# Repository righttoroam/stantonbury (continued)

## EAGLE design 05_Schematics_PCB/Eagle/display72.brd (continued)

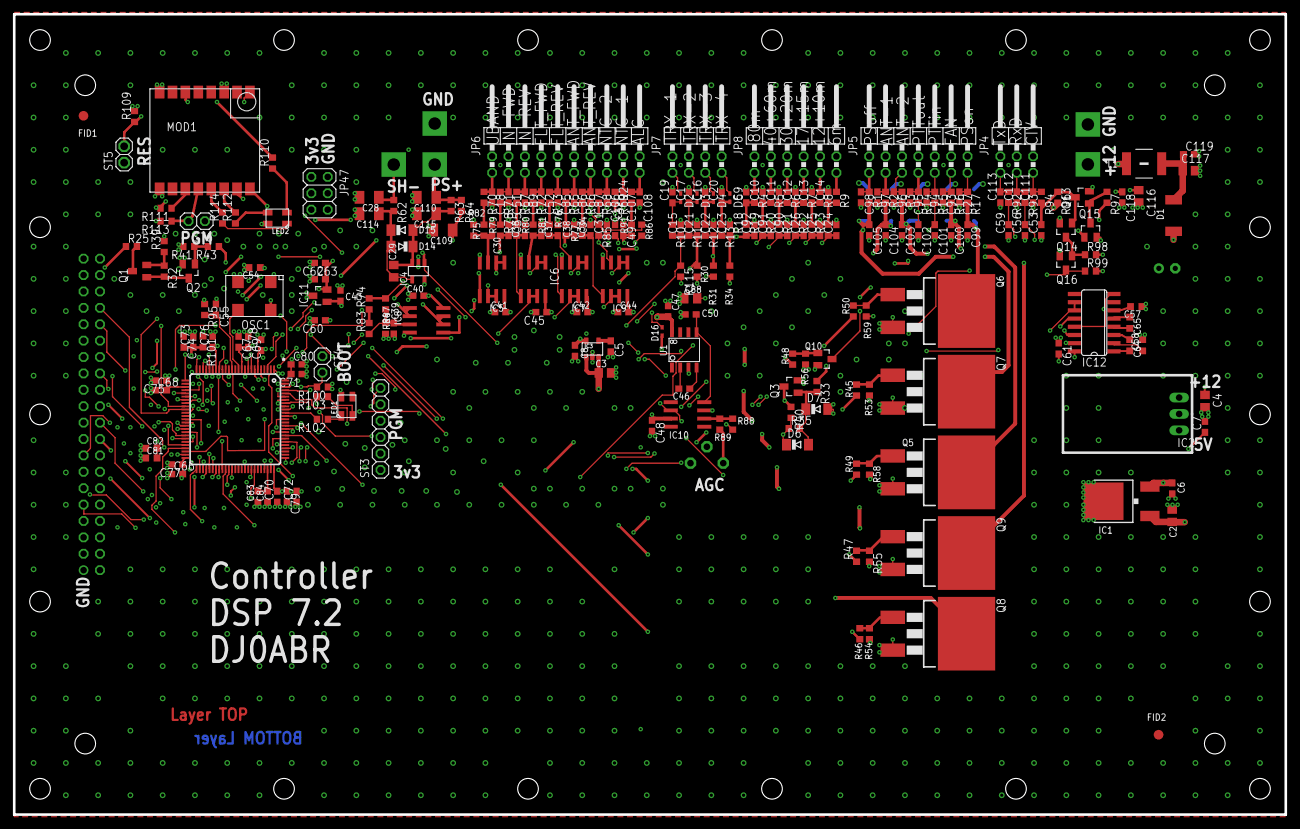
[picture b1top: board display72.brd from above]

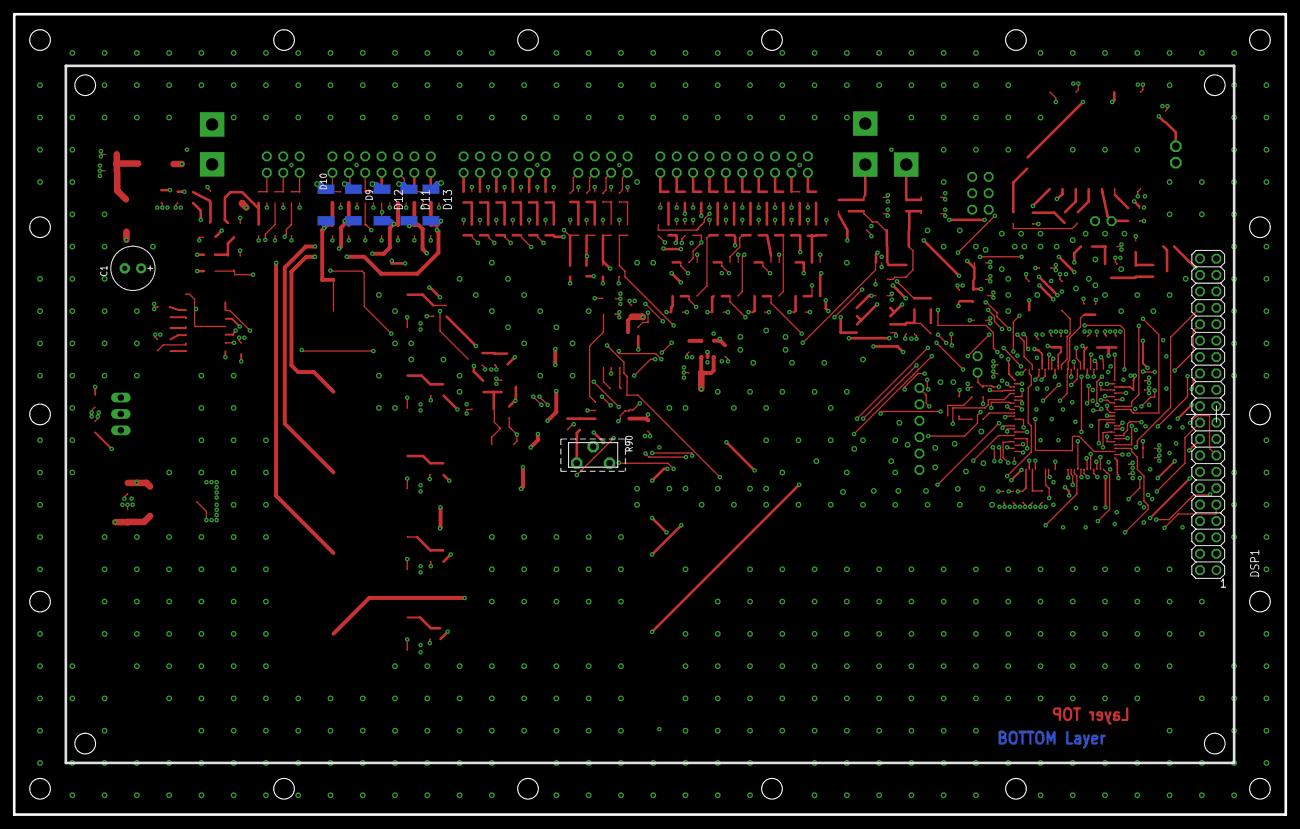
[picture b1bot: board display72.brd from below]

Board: 4 copper layers, 197.0 x 124.0 mm, 280 parts (10 on the bottom side), 198 nets.

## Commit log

2020-11-07 added file structure and heatsink spreadsheet
2020-11-07 test
2020-11-07 added dummy files
2020-11-07 added firmware from DJ0ABR at v1.8
2020-11-08 tidy up, add scehmatics
2020-11-08 updated gitignore
2020-11-09 Updated pin assignments
2020-11-09 Added datasheets, calcs and target spec
2020-11-09 Replaced feasibility spreadsheet with mass est
2020-11-10 More reference materials
2020-11-10 Added ref info on Razvans 600W design
2020-11-11 Controller PCB added
2020-11-28 lastet files added
